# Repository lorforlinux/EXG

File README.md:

# EXG
ADS1292 based EXG device.

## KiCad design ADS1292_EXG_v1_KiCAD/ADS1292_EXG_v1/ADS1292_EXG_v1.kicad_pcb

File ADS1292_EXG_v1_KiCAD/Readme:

#################
 !!! Not Final !!!
 #################
 
 These kiCAD files are just for getting insights into the first prototype of the breakout and it lacks details and footprint files. If you want to edit the schematic you must install the required footprints from site like component search. I am planning to make new versions as i progress and I want you to keep checking on this repo if you are interested in contributing to this project, we can talk on issue tracker OR you can contact me on my email (deepaklorkhatri7@gmail.com).

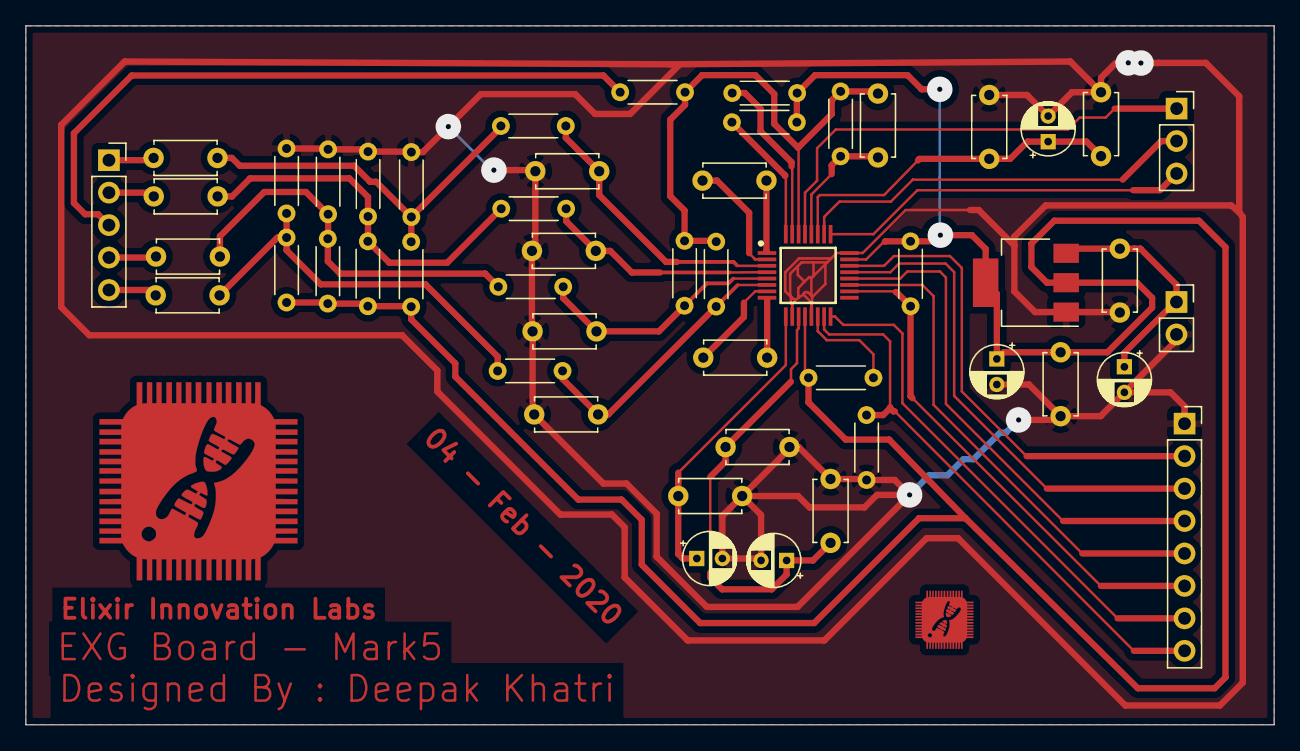
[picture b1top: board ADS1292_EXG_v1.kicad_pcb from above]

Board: 2 copper layers, 97.7 x 54.7 mm, 50 parts (0 on the bottom side), 38 nets.

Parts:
C1, C2, C3, C4, C5, C6, C7, C8, C9, C10, C12, C13, C15, C16, C18, C19, C21, C22: C; C_Disc_D4.7mm_W2.5mm_P5.00mm
C11, C14, C17, C20, C23: CP; CP_Radial_D4.0mm_P2.00mm
IC1: ADS1292IPBS; QFP50P700X700X120-32N
J1: Conn_01x05_Male; PinSocket_1x05_P2.54mm_Vertical
J2: Conn_01x03_Male; PinSocket_1x03_P2.54mm_Vertical
J3: Conn_01x08_Male; PinSocket_1x08_P2.54mm_Vertical
J5: Conn_01x02_Male; PinSocket_1x02_P2.54mm_Vertical
R1, R2, R3, R4, R5, R6, R7, R8, R9, R10, R11, R12, R13, R14, R15, R16, R17, R18, R19, R20, R21: R; R_Axial_DIN0204_L3.6mm_D1.6mm_P5.08mm_Horizontal
U1: AP1117-33; SOT-223-3_TabPin2

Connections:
1N: C1.1, J1.1
1P: C2.1, J1.2
2N: C3.1, J1.4
2P: C4.1, J1.5
CS: IC1.18, J3.6, R21.2
DIN: IC1.19, J3.5
DOUT: IC1.21, J3.3
DRDY: IC1.22, J3.2
GND: C5.1, C6.1, C7.1, C8.1, C11.2, C12.1, C13.1, C14.2, C15.1, C17.2, C18.1, C19.1, C20.2, C21.2, C22.2, C23.2, IC1.10, IC1.13, IC1.24, J3.1, J5.2, R1.2, R3.2, R6.2, R8.2, R20.1, U1.1
GPIO1: IC1.26, J2.2
GPIO2: IC1.25, J2.3
unnamed: C1.2, R8.1, R9.2, R13.2
unnamed: C2.2, R6.1, R7.2, R10.2
unnamed: C3.2, R3.1, R4.2, R11.2
unnamed: C4.2, R1.1, R2.2, R12.2
unnamed: C5.2, IC1.5, R11.1, R14.1
unnamed: C6.2, IC1.3, R13.1
unnamed: C7.2, IC1.4, R10.1
unnamed: C8.2, IC1.6, R12.1, R15.1
unnamed: C9.1, IC1.1
unnamed: C9.2, IC1.2
unnamed: C10.1, IC1.8
unnamed: C10.2, IC1.7
unnamed: C11.1, C12.2, IC1.9
unnamed: C13.2, C14.1, C15.2, IC1.11
unnamed: C16.1, IC1.28, R19.1
unnamed: C17.1, C18.2, C19.2, IC1.27
unnamed: IC1.14, R18.2
unnamed: IC1.31, R17.2
unnamed: IC1.32, R16.2
unnamed: J1.3, R5.2
RESET: IC1.15, J3.8, R20.2
RLD: C16.2, IC1.30, R5.1, R14.2, R15.2, R19.2
SCLK: IC1.20, J3.4
START: IC1.16, J3.7
TEST: IC1.29, J2.1
VCC: C20.1, C21.1, J5.1, U1.3
VDD: C22.1, C23.1, IC1.12, IC1.23, R2.1, R4.1, R7.1, R9.1, R16.1, R17.1, R18.1, R21.1, U1.2

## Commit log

2020-04-13 add kiCAD files
2020-04-14 add firmware for channel data
